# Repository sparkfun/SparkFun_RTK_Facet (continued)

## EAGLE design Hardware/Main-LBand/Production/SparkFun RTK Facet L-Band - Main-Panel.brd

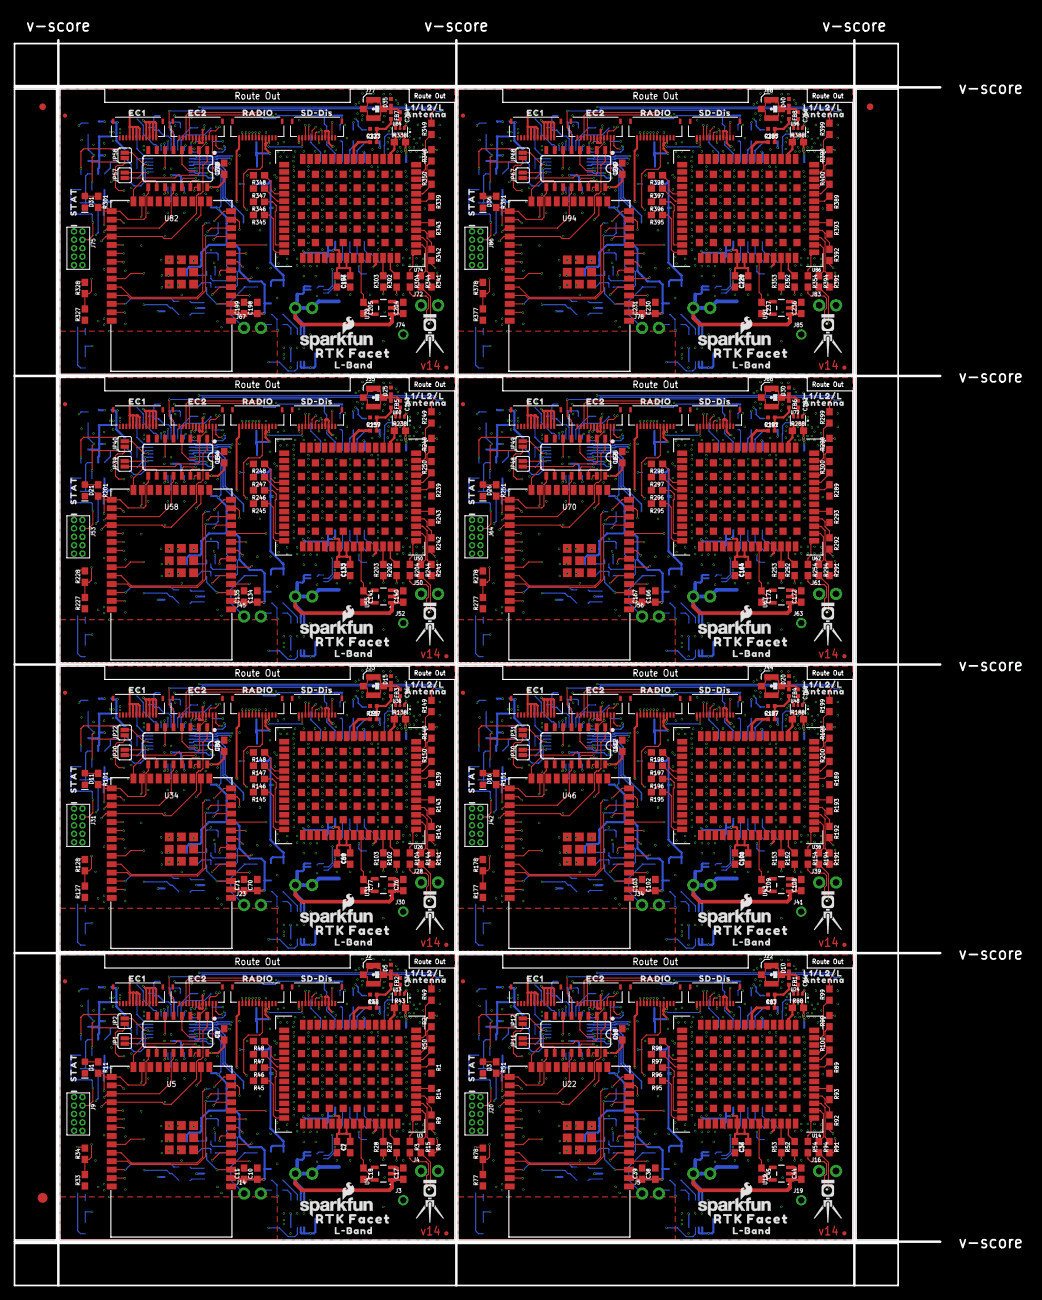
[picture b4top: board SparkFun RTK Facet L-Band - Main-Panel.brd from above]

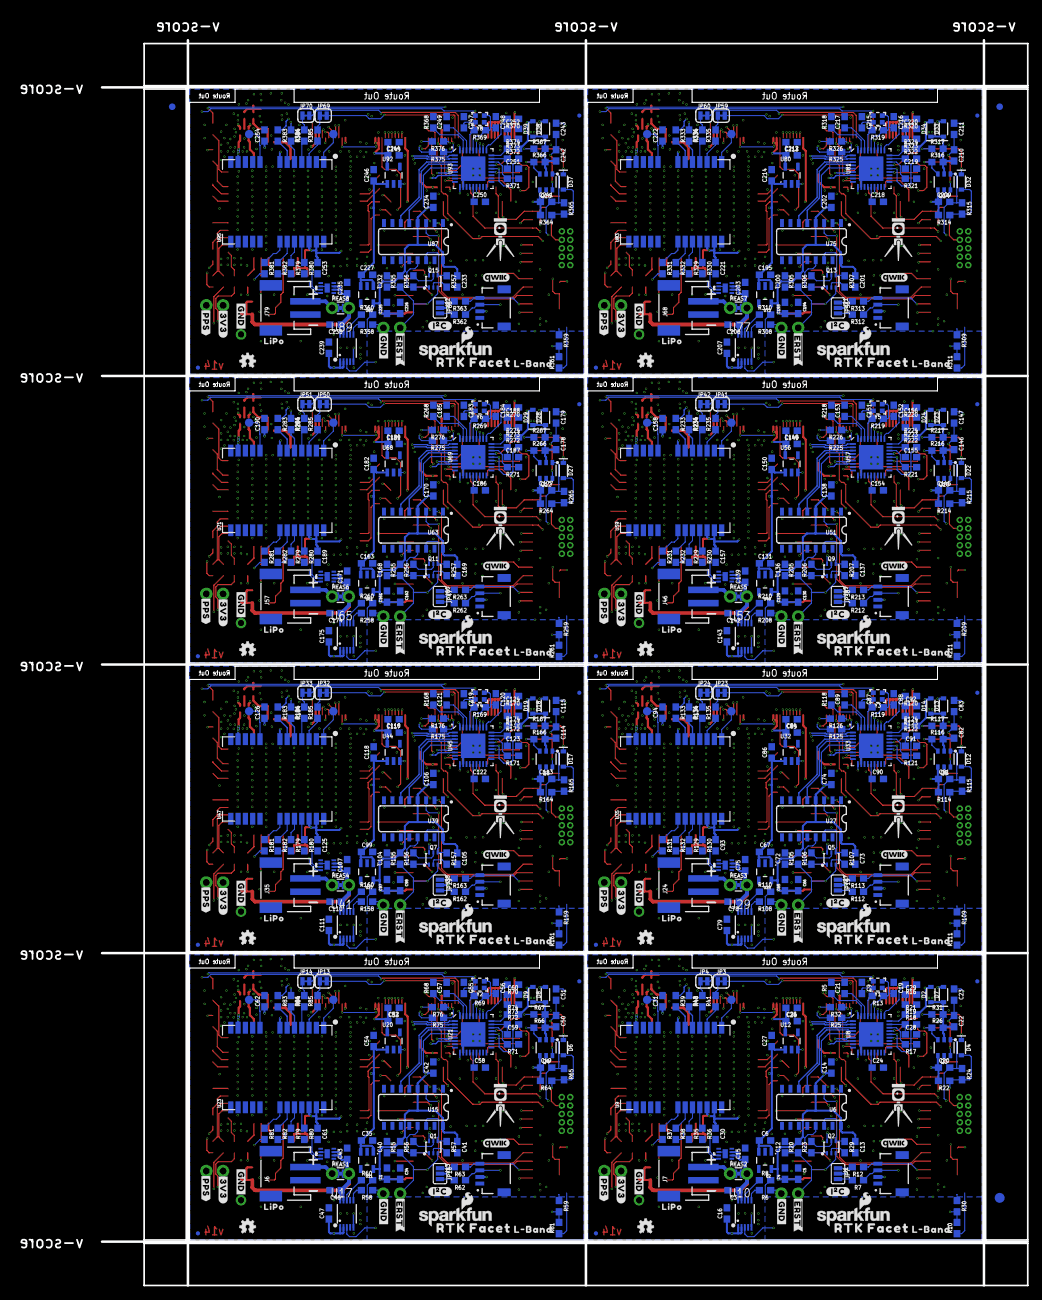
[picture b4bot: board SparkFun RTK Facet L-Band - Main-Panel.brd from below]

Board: 4 copper layers, 139.6 x 187.7 mm, 1206 parts (715 on the bottom side), 872 nets.

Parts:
C1, C2, C4, C6, C17, C18, C25, C27, C30, C31, C35, C36, C44, C45, C52, C54, C61, C62, C65, C67, C68, C76, C77, C84, C86, C93, C94, C97, C99, C100, C108, C109, C116, C118, C125, C126, C129, C131, C132, C140, C141, C148, C150, C157, C158, C161, C163, C164, C172, C173, C180, C182, C189, C190, C193, C195, C196, C204, C205, C212, C214, C221, C222, C225, C227, C228, C236, C237, C244, C246, C253, C254: 1.0uF; 0603
C3, C16, C46, C47, C78, C79, C110, C111, C142, C143, C174, C175, C206, C207, C238, C239: 4.7uF; 0603
C5, C7, C8, C11, C12, C13, C15, C21, C22, C23, C24, C26, C28, C29, C34, C37, C39, C40, C41, C43, C48, C50, C51, C53, C57, C58, C59, C60, C66, C69, C71, C72, C73, C75, C80, C82, C83, C85, C89, C90, C91, C92, C98, C101, C103, C104, C105, C107, C112, C114, C115, C117, C121, C122, C123, C124, C130, C133, C135, C136, C137, C139, C144, C146, C147, C149, C153, C154, C155, C156, C162, C165, C167, C168, C169, C171, C176, C178, C179, C181, C185, C186, C187, C188, C194, C197, C199, C200, C201, C203, C208, C210, C211, C213, C217, C218, C219, C220, C226, C229, C231, C232, C233, C235, C240, C242, C243, C245, C249, C250, C251, C252: 0.1uF; 0603
C9, C19, C55, C56, C87, C88, C119, C120, C151, C152, C183, C184, C215, C216, C247, C248: 18pF; 0603
C10, C14, C20, C38, C42, C49, C70, C74, C81, C102, C106, C113, C134, C138, C145, C166, C170, C177, C198, C202, C209, C230, C234, C241: 10uF; 0603
C32, C33, C63, C64, C95, C96, C127, C128, C159, C160, C191, C192, C223, C224, C255, C256: 47pF; 0402-TIGHT
D1, D3, D11, D16, D21, D26, D31, D36: Yellow; LED-0603
D2, D7, D8, D9, D13, D14, D18, D19, D23, D24, D28, D29, D33, D34, D38, D39: 3A/10V/280mV; SOD-323
D4, D6, D12, D17, D22, D27, D32, D37: 250mA/100V; SOD-323
D5, D10, D15, D20, D25, D30, D35, D40: PESD0402; 0402-TIGHT
E$1, E$2, E$3, E$4: FIDUCIAL-1X2
E$5, E$6: FIDUCIAL-1.5X3
FB1, FB2, FB3, FB4, FB5, FB6, FB7, FB8: 2.66Ω; 0402-TIGHT
J1, J13, J27, J38, J49, J60, J71, J82: QWIIC_RIGHT_ANGLE; JST04_1MM_RA
J2, J22, J33, J44, J55, J66, J77, J88: U.FL
J3, J19, J30, J41, J52, J63, J74, J85: 1X01_NO_SILK
J4, J5, J14, J16, J23, J28, J34, J39, J45, J50, J56, J61, J67, J72, J78, J83: 1X02_NO_SILK
J6, J7, J24, J35, J46, J57, J68, J79: JST-2-SMD
J8, J10, J11, J12, J15, J17, J18, J21, J25, J26, J29, J32, J36, J37, J40, J43, J47, J48, J51, J54, J58, J59, J62, J65, J69, J70, J73, J76, J80, J81, J84, J87: FPC_12_DOUBLESIDED_BACKFLIP
J9, J20, J31, J42, J53, J64, J75, J86: CORTEX_JTAG_DEBUG_PTH; 2X5-PTH-1.27MM
JP1, JP2, JP11, JP12, JP20, JP22, JP30, JP31, JP39, JP40, JP48, JP49, JP57, JP58, JP67, JP68: SMT-JUMPER_2_NO_SILK
JP3, JP4, JP13, JP14, JP23, JP24, JP32, JP33, JP41, JP42, JP50, JP51, JP59, JP60, JP69, JP70: SMT-JUMPER_2_NC_TRACE_SILK
JP5, JP6, JP8, JP9, JP15, JP16, JP17, JP18, JP21, JP25, JP26, JP27, JP28, JP34, JP35, JP36, JP37, JP43, JP44, JP45, JP46, JP52, JP53, JP54, JP55, JP61, JP62, JP63, JP64, JP65, JP71, JP81: FIDUCIALUFIDUCIAL; FIDUCIAL-MICRO
JP7, JP10, JP19, JP29, JP38, JP47, JP56, JP66: JUMPER-SMT_3_NO_SILK; SMT-JUMPER_3_NO_SILK
LOGO1, LOGO4, LOGO7, LOGO10, LOGO13, LOGO16, LOGO19, LOGO22: OSHW-LOGOMINI; OSHW-LOGO-MINI
LOGO2, LOGO3, LOGO5, LOGO6, LOGO8, LOGO9, LOGO11, LOGO12, LOGO14, LOGO15, LOGO17, LOGO18, LOGO20, LOGO21, LOGO23, LOGO24: SFE_LOGO_NAME_FLAME.1_INCH; SFE_LOGO_NAME_FLAME_.1
MEAS1, MEAS2, MEAS3, MEAS4, MEAS5, MEAS6, MEAS7, MEAS8: JUMPER-COMBO_2_NC_TRACE; COMBO-JUMPER_2_NC_TRACE
Q1, Q2, Q5, Q7, Q9, Q11, Q13, Q15: MBT3904DW1T1; SC70-6
Q3, Q4, Q6, Q8, Q10, Q12, Q14, Q16: SIL2308; SOT26
R1, R2, R3, R4, R9, R14, R15, R35, R36, R37, R38, R41, R42, R45, R46, R47, R48, R49, R50, R54, R79, R80, R81, R82, R85, R86, R89, R90, R91, R92, R93, R94, R95, R96, R97, R98, R99, R100, R104, R129, R130, R131, R132, R135, R136, R139, R140, R141, R142, R143, R144, R145, R146, R147, R148, R149, R150, R154, R179, R180, R181, R182, R185, R186, R189, R190, R191, R192, R193, R194, R195, R196, R197, R198, R199, R200, R204, R229, R230, R231, R232, R235, R236, R239, R240, R241, R242, R243, R244, R245, R246, R247, R248, R249, R250, R254, R279, R280, R281, R282, R285, R286, R289, R290, R291, R292, R293, R294, R295, R296, R297, R298, R299, R300, R304, R329, R330, R331, R332, R335, R336, R339, R340, R341, R342, R343, R344, R345, R346, R347, R348, R349, R350, R354, R379, R380, R381, R382, R385, R386, R389, R390, R391, R392, R393, R394, R395, R396, R397, R398, R399, R400: 33; 0603
R5, R68, R118, R168, R218, R268, R318, R368: 12k; 0603
R6, R11, R51, R58, R101, R108, R151, R158, R201, R208, R251, R258, R301, R308, R351, R358: 1k; 0603
R7, R12, R62, R63, R112, R113, R162, R163, R212, R213, R262, R263, R312, R313, R362, R363: 2.2k; 0603
R8, R60, R110, R160, R210, R260, R310, R360: 0; 0603
R10, R20, R22, R23, R29, R31, R34, R55, R56, R57, R61, R64, R67, R78, R105, R106, R107, R111, R114, R117, R128, R155, R156, R157, R161, R164, R167, R178, R205, R206, R207, R211, R214, R217, R228, R255, R256, R257, R261, R264, R267, R278, R305, R306, R307, R311, R314, R317, R328, R355, R356, R357, R361, R364, R367, R378: 10k; 0603
R13, R69, R119, R169, R219, R269, R319, R369: 1M; 0603
R16, R17, R18, R19, R21, R26, R33, R66, R70, R71, R72, R73, R74, R77, R116, R120, R121, R122, R123, R124, R127, R166, R170, R171, R172, R173, R174, R177, R216, R220, R221, R222, R223, R224, R227, R266, R270, R271, R272, R273, R274, R277, R316, R320, R321, R322, R323, R324, R327, R366, R370, R371, R372, R373, R374, R377: 100k; 0603
R24, R65, R115, R165, R215, R265, R315, R365: 300k; 0603
R25, R32, R75, R76, R125, R126, R175, R176, R225, R226, R275, R276, R325, R326, R375, R376: 22; 0603
R27, R28, R39, R40, R52, R53, R83, R84, R102, R103, R133, R134, R152, R153, R183, R184, R202, R203, R233, R234, R252, R253, R283, R284, R302, R303, R333, R334, R352, R353, R383, R384: 27; 0603
R30, R59, R109, R159, R209, R259, R309, R359: 150k; 0603
R43, R88, R138, R188, R238, R288, R338, R388: 100; 0603
R44, R87, R137, R187, R237, R287, R337, R387: 10; 0402-TIGHT
TP1, TP2, TP3, TP4, TP5, TP6, TP7, TP8, TP9, TP10, TP11, TP12, TP13, TP14, TP15, TP16: TEST-POINT3X5; PAD.03X.05
U1, U18, U30, U42, U54, U66, U78, U90: 74HC4052D; SO16
U2, U11, U12, U20, U25, U32, U37, U44, U49, U56, U61, U68, U73, U80, U85, U92: AP2112K-3.3V; SOT23-5
U3, U14, U26, U38, U50, U62, U74, U86: U-BLOX_ZED-F9P; ZED-F9P
U4, U19, U31, U43, U55, U67, U79, U91: STLQ015-3.3V; SOT23-5
U5, U22, U34, U46, U58, U70, U82, U94: ESP-WROOM-3232D-DFMP; ESP-WROOM-32D-DFM_PASTE
U6, U15, U27, U39, U51, U63, U75, U87: CH340C; SO016
U7, U16, U28, U40, U52, U64, U76, U88: MAX17048; DFN-8
U8, U21, U33, U45, U57, U69, U81, U93: USB251XB; QFN-36
U9, U23, U35, U47, U59, U71, U83, U95: U-BLOX_NEO-D9S-00B; NEO-M9N/M8T/M8U/D9S/F9P
U10, U17, U29, U41, U53, U65, U77, U89: MCP73833MSOP; MSOP10
U13, U24, U36, U48, U60, U72, U84, U96: POWER-DIVIDER; PD0922J5050S2HF_ANA
U$1, U$22, U$47, U$68, U$90, U$111, U$132, U$153: LIPO0
U$2, U$30, U$42, U$63, U$85, U$106, U$127, U$148: QWIIC_4MM
U$3, U$20, U$45, U$66, U$88, U$109, U$130, U$151: EC21
U$4, U$21, U$46, U$67, U$89, U$110, U$131, U$152: SD#DIS0
U$5, U$7, U$40, U$41, U$61, U$62, U$82, U$83, U$104, U$105, U$125, U$126, U$146, U$147, U$167, U$168: L#BAND0
U$6, U$23, U$48, U$69, U$91, U$112, U$133, U$154: #3V3#0
U$8, U$19, U$44, U$65, U$87, U$108, U$129, U$150: EC10
U$9, U$14, U$35, U$43, U$56, U$64, U$77, U$84, U$86, U$99, U$107, U$120, U$128, U$141, U$149, U$162: #GND#1
U$10, U$27, U$49, U$70, U$92, U$113, U$134, U$155: #PPS#1
U$11, U$13, U$32, U$34, U$53, U$55, U$74, U$76, U$96, U$98, U$117, U$119, U$138, U$140, U$159, U$161: RTK_FACET0
U$12, U$33, U$54, U$75, U$97, U$118, U$139, U$160: RADIO0
U$15, U$16, U$36, U$37, U$57, U$58, U$78, U$79, U$100, U$101, U$121, U$122, U$142, U$143, U$163, U$164: RTK5#SVG0
U$17, U$38, U$59, U$80, U$102, U$123, U$144, U$165: ANTENNA1
U$18, U$39, U$60, U$81, U$103, U$124, U$145, U$166: L1#L2#L0
U$24, U$28, U$50, U$71, U$93, U$114, U$135, U$156: STAT0
U$25, U$29, U$51, U$72, U$94, U$115, U$136, U$157: #I�C#0
U$26, U$31, U$52, U$73, U$95, U$116, U$137, U$158: ##ERST##0
Y1, Y2, Y3, Y4, Y5, Y6, Y7, Y8: 24MHz; CRYSTAL-SMD-2.0X1.6MM

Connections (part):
3.3V: C2.1, C7.2, C8.1, C25.1, C26.2, C30.1, C31.1, J1.2, J4.1, J8.3, J8.4, J10.3, J10.4, J18.5, J18.6, JP7.2, U1.16, U3.33, U3.34, U3.38, U9.7, U9.22, U9.23, U12.5
3.3V1: C36.1, C37.2, C48.1, C52.1, C53.2, C61.1, C62.1, J12.5, J12.6, J13.2, J16.1, J17.3, J17.4, J21.3, J21.4, JP10.2, U14.33, U14.34, U14.38, U18.16, U20.5, U23.7, U23.22, U23.23
3.3V2: C68.1, C69.2, C80.1, C84.1, C85.2, C93.1, C94.1, J26.5, J26.6, J27.2, J28.1, J29.3, J29.4, J32.3, J32.4, JP19.2, U26.33, U26.34, U26.38, U30.16, U32.5, U35.7, U35.22, U35.23
3.3V3: C100.1, C101.2, C112.1, C116.1, C117.2, C125.1, C126.1, J37.5, J37.6, J38.2, J39.1, J40.3, J40.4, J43.3, J43.4, JP29.2, U38.33, U38.34, U38.38, U42.16, U44.5, U47.7, U47.22, U47.23
3.3V4: C132.1, C133.2, C144.1, C148.1, C149.2, C157.1, C158.1, J48.5, J48.6, J49.2, J50.1, J51.3, J51.4, J54.3, J54.4, JP38.2, U50.33, U50.34, U50.38, U54.16, U56.5, U59.7, U59.22, U59.23
3.3V5: C164.1, C165.2, C176.1, C180.1, C181.2, C189.1, C190.1, J59.5, J59.6, J60.2, J61.1, J62.3, J62.4, J65.3, J65.4, JP47.2, U62.33, U62.34, U62.38, U66.16, U68.5, U71.7, U71.22, U71.23
3.3V6: C196.1, C197.2, C208.1, C212.1, C213.2, C221.1, C222.1, J70.5, J70.6, J71.2, J72.1, J73.3, J73.4, J76.3, J76.4, JP56.2, U74.33, U74.34, U74.38, U78.16, U80.5, U83.7, U83.22, U83.23
3.3V7: C228.1, C229.2, C240.1, C244.1, C245.2, C253.1, C254.1, J81.5, J81.6, J82.2, J83.1, J84.3, J84.4, J87.3, J87.4, JP66.2, U86.33, U86.34, U86.38, U90.16, U92.5, U95.7, U95.22, U95.23
CHG_LED: J8.11, U10.3
CHG_LED1: J17.11, U17.3
CHG_LED2: J29.11, U29.3
CHG_LED3: J40.11, U41.3
CHG_LED4: J51.11, U53.3
CHG_LED5: J62.11, U65.3
CHG_LED6: J73.11, U77.3
CHG_LED7: J84.11, U89.3
CHG_THERM1: R8.2, R10.2, R30.2
CHG_THERM2: R59.2, R60.2, R61.2
CHG_THERM3: R109.2, R110.2, R111.2
CHG_THERM4: R159.2, R160.2, R161.2
CHG_THERM5: R209.2, R210.2, R211.2
CHG_THERM6: R259.2, R260.2, R261.2
CHG_THERM7: R309.2, R310.2, R311.2
CHG_THERM8: R359.2, R360.2, R361.2
ESP32_!DTR: Q2.1, R23.1, U6.13
ESP32_!DTR1: Q1.1, R56.1, U15.13
ESP32_!DTR2: Q5.1, R106.1, U27.13
ESP32_!DTR3: Q7.1, R156.1, U39.13
ESP32_!DTR4: Q9.1, R206.1, U51.13
ESP32_!DTR5: Q11.1, R256.1, U63.13
ESP32_!DTR6: Q13.1, R306.1, U75.13
ESP32_!DTR7: Q15.1, R356.1, U87.13
ESP32_!RTS: Q2.4, R29.1, U6.14
ESP32_!RTS1: Q1.4, R57.1, U15.14
ESP32_!RTS2: Q5.4, R107.1, U27.14
ESP32_!RTS3: Q7.4, R157.1, U39.14
ESP32_!RTS4: Q9.4, R207.1, U51.14
ESP32_!RTS5: Q11.4, R257.1, U63.14
ESP32_!RTS6: Q13.4, R307.1, U75.14
ESP32_!RTS7: Q15.4, R357.1, U87.14
ESP32_EN: C12.1, J9.10, J14.1, Q2.3, R20.1, U5.3
ESP32_EN1: C40.1, J5.1, J20.10, Q1.3, R55.1, U22.3
ESP32_EN2: C72.1, J23.1, J31.10, Q5.3, R105.1, U34.3
ESP32_EN3: C104.1, J34.1, J42.10, Q7.3, R155.1, U46.3
ESP32_EN4: C136.1, J45.1, J53.10, Q9.3, R205.1, U58.3
ESP32_EN5: C168.1, J56.1, J64.10, Q11.3, R255.1, U70.3
ESP32_EN6: C200.1, J67.1, J75.10, Q13.3, R305.1, U82.3
ESP32_EN7: C232.1, J78.1, J86.10, Q15.3, R355.1, U94.3
ESP32_RXI: U5.34, U6.2
ESP32_RXI1: U15.2, U22.34
ESP32_RXI2: U27.2, U34.34
ESP32_RXI3: U39.2, U46.34
ESP32_RXI4: U51.2, U58.34
ESP32_RXI5: U63.2, U70.34
ESP32_RXI6: U75.2, U82.34
ESP32_RXI7: U87.2, U94.34
ESP32_TXO: U5.35, U6.3
ESP32_TXO1: U15.3, U22.35
ESP32_TXO2: U27.3, U34.35
ESP32_TXO3: U39.3, U46.35
ESP32_TXO4: U51.3, U58.35
ESP32_TXO5: U63.3, U70.35
ESP32_TXO6: U75.3, U82.35
ESP32_TXO7: U87.3, U94.35
ESP_0/BOOT/STAT_LED/MUX_B: Q2.6, R11.2, U1.9, U5.25
ESP_0/BOOT/STAT_LED/MUX_B1: Q1.6, R51.2, U18.9, U22.25
ESP_0/BOOT/STAT_LED/MUX_B2: Q5.6, R101.2, U30.9, U34.25
ESP_0/BOOT/STAT_LED/MUX_B3: Q7.6, R151.2, U42.9, U46.25
ESP_0/BOOT/STAT_LED/MUX_B4: Q9.6, R201.2, U54.9, U58.25
ESP_0/BOOT/STAT_LED/MUX_B5: Q11.6, R251.2, U66.9, U70.25
ESP_0/BOOT/STAT_LED/MUX_B6: Q13.6, R301.2, U78.9, U82.25
ESP_0/BOOT/STAT_LED/MUX_B7: Q15.6, R351.2, U90.9, U94.25
ESP_2/MUX_A: U1.10, U5.24
ESP_2/MUX_A1: U18.10, U22.24
ESP_2/MUX_A2: U30.10, U34.24
ESP_2/MUX_A3: U42.10, U46.24
ESP_2/MUX_A4: U54.10, U58.24
ESP_2/MUX_A5: U66.10, U70.24
ESP_2/MUX_A6: U78.10, U82.24
ESP_2/MUX_A7: U90.10, U94.24
ESP_3V1: C1.1, C34.2, C38.1, C39.1, C41.1, C42.1, J20.1, R55.2, R72.2, R78.2, U11.5, U15.4, U15.16, U21.5, U21.10, U21.15, U21.23, U21.29, U21.36, U22.2
ESP_3V2: C65.1, C66.2, C70.1, C71.1, C73.1, C74.1, J31.1, R105.2, R122.2, R128.2, U25.5, U27.4, U27.16, U33.5, U33.10, U33.15, U33.23, U33.29, U33.36, U34.2
ESP_3V3: C4.1, C5.2, C10.1, C11.1, C13.1, C14.1, J9.1, R18.2, R20.2, R34.2, U2.5, U5.2, U6.4, U6.16, U8.5, U8.10, U8.15, U8.23, U8.29, U8.36
ESP_3V4: C97.1, C98.2, C102.1, C103.1, C105.1, C106.1, J42.1, R155.2, R172.2, R178.2, U37.5, U39.4, U39.16, U45.5, U45.10, U45.15, U45.23, U45.29, U45.36, U46.2
ESP_3V5: C129.1, C130.2, C134.1, C135.1, C137.1, C138.1, J53.1, R205.2, R222.2, R228.2, U49.5, U51.4, U51.16, U57.5, U57.10, U57.15, U57.23, U57.29, U57.36, U58.2
ESP_3V6: C161.1, C162.2, C166.1, C167.1, C169.1, C170.1, J64.1, R255.2, R272.2, R278.2, U61.5, U63.4, U63.16, U69.5, U69.10, U69.15, U69.23, U69.29, U69.36, U70.2
ESP_3V7: C193.1, C194.2, C198.1, C199.1, C201.1, C202.1, J75.1, R305.2, R322.2, R328.2, U73.5, U75.4, U75.16, U81.5, U81.10, U81.15, U81.23, U81.29, U81.36, U82.2
ESP_3V8: C225.1, C226.2, C230.1, C231.1, C233.1, C234.1, J86.1, R355.2, R372.2, R378.2, U85.5, U87.4, U87.16, U93.5, U93.10, U93.15, U93.23, U93.29, U93.36, U94.2
ESP_4/RADIO_PWR_ON: J10.6, U5.26
ESP_4/RADIO_PWR_ON1: J21.6, U22.26
ESP_4/RADIO_PWR_ON2: J32.6, U34.26
ESP_4/RADIO_PWR_ON3: J43.6, U46.26
ESP_4/RADIO_PWR_ON4: J54.6, U58.26
ESP_4/RADIO_PWR_ON5: J65.6, U70.26
ESP_4/RADIO_PWR_ON6: J76.6, U82.26
ESP_4/RADIO_PWR_ON7: J87.6, U94.26
ESP_5/RADIO_CTSI: J10.8, U5.29
ESP_5/RADIO_CTSI1: J21.8, U22.29
ESP_5/RADIO_CTSI2: J32.8, U34.29
ESP_5/RADIO_CTSI3: J43.8, U46.29
ESP_5/RADIO_CTSI4: J54.8, U58.29
ESP_5/RADIO_CTSI5: J65.8, U70.29
ESP_5/RADIO_CTSI6: J76.8, U82.29
ESP_5/RADIO_CTSI7: J87.8, U94.29
ESP_12/MTDI: J9.8, U5.14
ESP_12/MTDI1: J20.8, U22.14
ESP_12/MTDI2: J31.8, U34.14
ESP_12/MTDI3: J42.8, U46.14
ESP_12/MTDI4: J53.8, U58.14
ESP_12/MTDI5: J64.8, U70.14
ESP_12/MTDI6: J75.8, U82.14
ESP_12/MTDI7: J86.8, U94.14
ESP_13/POWER_CTRL/MTCK: D4.A, J9.4, R22.1, R24.2, U5.16
ESP_13/POWER_CTRL/MTCK1: D6.A, J20.4, R64.1, R65.2, U22.16
ESP_13/POWER_CTRL/MTCK2: D12.A, J31.4, R114.1, R115.2, U34.16
ESP_13/POWER_CTRL/MTCK3: D17.A, J42.4, R164.1, R165.2, U46.16
ESP_13/POWER_CTRL/MTCK4: D22.A, J53.4, R214.1, R215.2, U58.16
ESP_13/POWER_CTRL/MTCK5: D27.A, J64.4, R264.1, R265.2, U70.16
ESP_13/POWER_CTRL/MTCK6: D32.A, J75.4, R314.1, R315.2, U82.16
ESP_13/POWER_CTRL/MTCK7: D37.A, J86.4, R364.1, R365.2, U94.16
ESP_14/PERIPHERAL_POWER/MTMS: J9.2, U5.13, U12.3
ESP_14/PERIPHERAL_POWER/MTMS1: J20.2, U20.3, U22.13
ESP_14/PERIPHERAL_POWER/MTMS2: J31.2, U32.3, U34.13
ESP_14/PERIPHERAL_POWER/MTMS3: J42.2, U44.3, U46.13
ESP_14/PERIPHERAL_POWER/MTMS4: J53.2, U56.3, U58.13
ESP_14/PERIPHERAL_POWER/MTMS5: J64.2, U68.3, U70.13
ESP_14/PERIPHERAL_POWER/MTMS6: J75.2, U80.3, U82.13
ESP_14/PERIPHERAL_POWER/MTMS7: J86.2, U92.3, U94.13
ESP_15/MTDO/RADIO_!RESET!: J9.6, J10.5, U5.23
ESP_15/MTDO/RADIO_!RESET!1: J20.6, J21.5, U22.23
ESP_15/MTDO/RADIO_!RESET!2: J31.6, J32.5, U34.23
ESP_15/MTDO/RADIO_!RESET!3: J42.6, J43.5, U46.23
ESP_15/MTDO/RADIO_!RESET!4: J53.6, J54.5, U58.23
ESP_15/MTDO/RADIO_!RESET!5: J64.6, J65.5, U70.23
ESP_15/MTDO/RADIO_!RESET!6: J75.6, J76.5, U82.23
ESP_15/MTDO/RADIO_!RESET!7: J86.6, J87.5, U94.23
ESP_16/ZED_TXO1: R3.2, U1.12, U5.27
ESP_16/ZED_TXO2: R54.2, U18.12, U22.27
ESP_16/ZED_TXO3: R104.2, U30.12, U34.27
ESP_16/ZED_TXO4: R154.2, U42.12, U46.27
ESP_16/ZED_TXO5: R204.2, U54.12, U58.27
ESP_16/ZED_TXO6: R254.2, U66.12, U70.27
ESP_16/ZED_TXO7: R304.2, U78.12, U82.27
ESP_16/ZED_TXO8: R354.2, U90.12, U94.27
ESP_17/ZED_RXI1: R15.2, U1.1, U5.28
ESP_17/ZED_RXI2: R94.2, U18.1, U22.28
ESP_17/ZED_RXI3: R144.2, U30.1, U34.28
ESP_17/ZED_RXI4: R194.2, U42.1, U46.28
ESP_17/ZED_RXI5: R244.2, U54.1, U58.28
ESP_17/ZED_RXI6: R294.2, U66.1, U70.28
ESP_17/ZED_RXI7: R344.2, U78.1, U82.28
ESP_17/ZED_RXI8: R394.2, U90.1, U94.28
ESP_18/SD_SCK: J8.7, U5.30
ESP_18/SD_SCK1: J17.7, U22.30
ESP_18/SD_SCK2: J29.7, U34.30
ESP_18/SD_SCK3: J40.7, U46.30
ESP_18/SD_SCK4: J51.7, U58.30
ESP_18/SD_SCK5: J62.7, U70.30
ESP_18/SD_SCK6: J73.7, U82.30
ESP_18/SD_SCK7: J84.7, U94.30
ESP_19/SD_CIPO: J8.8, U5.31
ESP_19/SD_CIPO1: J17.8, U22.31
ESP_19/SD_CIPO2: J29.8, U34.31
ESP_19/SD_CIPO3: J40.8, U46.31
ESP_19/SD_CIPO4: J51.8, U58.31
ESP_19/SD_CIPO5: J62.8, U70.31
ESP_19/SD_CIPO6: J73.8, U82.31
ESP_19/SD_CIPO7: J84.8, U94.31
ESP_21/SDA: J1.3, J8.10, J18.4, JP1.1, R4.2, R7.1, R37.2, U1.2, U5.33, U7.8
ESP_21/SDA1: J12.4, J13.3, J17.10, JP11.1, R62.1, R81.2, R91.2, U16.8, U18.2, U22.33
ESP_21/SDA2: J26.4, J27.3, J29.10, JP20.1, R112.1, R131.2, R141.2, U28.8, U30.2, U34.33
ESP_21/SDA3: J37.4, J38.3, J40.10, JP30.1, R162.1, R181.2, R191.2, U40.8, U42.2, U46.33
ESP_21/SDA4: J48.4, J49.3, J51.10, JP39.1, R212.1, R231.2, R241.2, U52.8, U54.2, U58.33
ESP_21/SDA5: J59.4, J60.3, J62.10, JP48.1, R262.1, R281.2, R291.2, U64.8, U66.2, U70.33
ESP_21/SDA6: J70.4, J71.3, J73.10, JP57.1, R312.1, R331.2, R341.2, U76.8, U78.2, U82.33
ESP_21/SDA7: J81.4, J82.3, J84.10, JP67.1, R362.1, R381.2, R391.2, U88.8, U90.2, U94.33
ESP_22/SCL: J1.4, J8.9, J18.3, JP2.1, R9.2, R12.1, R38.2, U1.15, U5.36, U7.7
ESP_22/SCL1: J12.3, J13.4, J17.9, JP12.1, R63.1, R82.2, R92.2, U16.7, U18.15, U22.36
ESP_22/SCL2: J26.3, J27.4, J29.9, JP22.1, R113.1, R132.2, R142.2, U28.7, U30.15, U34.36
ESP_22/SCL3: J37.3, J38.4, J40.9, JP31.1, R163.1, R182.2, R192.2, U40.7, U42.15, U46.36
ESP_22/SCL4: J48.3, J49.4, J51.9, JP40.1, R213.1, R232.2, R242.2, U52.7, U54.15, U58.36
ESP_22/SCL5: J59.3, J60.4, J62.9, JP49.1, R263.1, R282.2, R292.2, U64.7, U66.15, U70.36
ESP_22/SCL6: J70.3, J71.4, J73.9, JP58.1, R313.1, R332.2, R342.2, U76.7, U78.15, U82.36
ESP_22/SCL7: J81.3, J82.4, J84.9, JP68.1, R363.1, R382.2, R392.2, U88.7, U90.15, U94.36
ESP_23/SD_COPI: J8.6, U5.37
ESP_23/SD_COPI1: J17.6, U22.37
ESP_23/SD_COPI2: J29.6, U34.37
ESP_23/SD_COPI3: J40.6, U46.37
ESP_23/SD_COPI4: J51.6, U58.37
ESP_23/SD_COPI5: J62.6, U70.37
ESP_23/SD_COPI6: J73.6, U82.37
ESP_23/SD_COPI7: J84.6, U94.37
ESP_25/SD_!CS!: J8.5, U5.10
ESP_25/SD_!CS!1: J17.5, U22.10
ESP_25/SD_!CS!2: J29.5, U34.10
ESP_25/SD_!CS!3: J40.5, U46.10
ESP_25/SD_!CS!4: J51.5, U58.10
ESP_25/SD_!CS!5: J62.5, U70.10
ESP_25/SD_!CS!6: J73.5, U82.10
ESP_25/SD_!CS!7: J84.5, U94.10
ESP_26/DAC1: U18.11, U22.11
ESP_26/DAC2: U1.11, U5.11
ESP_26/DAC3: U30.11, U34.11
ESP_26/DAC4: U42.11, U46.11
ESP_26/DAC5: U54.11, U58.11
ESP_26/DAC6: U66.11, U70.11
ESP_26/DAC7: U78.11, U82.11
ESP_26/DAC8: U90.11, U94.11
ESP_27/FAST_OFF: C20.2, Q3.G1, R24.1, U5.12
ESP_27/FAST_OFF1: C49.2, Q4.G1, R65.1, U22.12
ESP_27/FAST_OFF2: C81.2, Q6.G1, R115.1, U34.12
ESP_27/FAST_OFF3: C113.2, Q8.G1, R165.1, U46.12
ESP_27/FAST_OFF4: C145.2, Q10.G1, R215.1, U58.12
ESP_27/FAST_OFF5: C177.2, Q12.G1, R265.1, U70.12
ESP_27/FAST_OFF6: C209.2, Q14.G1, R315.1, U82.12
ESP_27/FAST_OFF7: C241.2, Q16.G1, R365.1, U94.12
ESP_32/RADIO_TXO: J10.11, U5.8
ESP_32/RADIO_TXO1: J21.11, U22.8
ESP_32/RADIO_TXO2: J32.11, U34.8
ESP_32/RADIO_TXO3: J43.11, U46.8
ESP_32/RADIO_TXO4: J54.11, U58.8
ESP_32/RADIO_TXO5: J65.11, U70.8
ESP_32/RADIO_TXO6: J76.11, U82.8
ESP_32/RADIO_TXO7: J87.11, U94.8
ESP_33/RADIO_RXI: J10.10, U5.9
ESP_33/RADIO_RXI1: J21.10, U22.9
ESP_33/RADIO_RXI2: J32.10, U34.9
ESP_33/RADIO_RXI3: J43.10, U46.9
ESP_33/RADIO_RXI4: J54.10, U58.9
ESP_33/RADIO_RXI5: J65.10, U70.9
ESP_33/RADIO_RXI6: J76.10, U82.9
ESP_33/RADIO_RXI7: J87.10, U94.9
ESP_DM: U6.6, U8.3
ESP_DM1: U15.6, U21.3
ESP_DM2: U27.6, U33.3
ESP_DM3: U39.6, U45.3
ESP_DM4: U51.6, U57.3
ESP_DM5: U63.6, U69.3
ESP_DM6: U75.6, U81.3
ESP_DM7: U87.6, U93.3
ESP_DP: U6.5, U8.4
ESP_DP1: U15.5, U21.4
ESP_DP2: U27.5, U33.4
ESP_DP3: U39.5, U45.4
ESP_DP4: U51.5, U57.4
ESP_DP5: U63.5, U69.4
ESP_DP6: U75.5, U81.4
ESP_DP7: U87.5, U93.4
ESP_I34/RADIO_INT: J10.7, U5.6
ESP_I34/RADIO_INT1: J21.7, U22.6
ESP_I34/RADIO_INT2: J32.7, U34.6
ESP_I34/RADIO_INT3: J43.7, U46.6
ESP_I34/RADIO_INT4: J54.7, U58.6
ESP_I34/RADIO_INT5: J65.7, U70.6
ESP_I34/RADIO_INT6: J76.7, U82.6
ESP_I34/RADIO_INT7: J87.7, U94.6
ESP_I35/DEVICE_SENSE: R33.2, R34.1, U5.7
ESP_I35/DEVICE_SENSE1: R77.2, R78.1, U22.7
ESP_I35/DEVICE_SENSE2: R127.2, R128.1, U34.7
ESP_I35/DEVICE_SENSE3: R177.2, R178.1, U46.7
ESP_I35/DEVICE_SENSE4: R227.2, R228.1, U58.7
ESP_I35/DEVICE_SENSE5: R277.2, R278.1, U70.7
ESP_I35/DEVICE_SENSE6: R327.2, R328.1, U82.7
ESP_I35/DEVICE_SENSE7: R377.2, R378.1, U94.7
ESP_I36/RADIO_RTSO: J10.9, U5.4
ESP_I36/RADIO_RTSO1: J21.9, U22.4
ESP_I36/RADIO_RTSO2: J32.9, U34.4
ESP_I36/RADIO_RTSO3: J43.9, U46.4
ESP_I36/RADIO_RTSO4: J54.9, U58.4
ESP_I36/RADIO_RTSO5: J65.9, U70.4
ESP_I36/RADIO_RTSO6: J76.9, U82.4
ESP_I36/RADIO_RTSO7: J87.9, U94.4
ESP_I39/ADC1: U18.4, U22.5
ESP_I39/ADC2: U30.4, U34.5
ESP_I39/ADC3: U42.4, U46.5
ESP_I39/ADC4: U54.4, U58.5
ESP_I39/ADC5: U66.4, U70.5
ESP_I39/ADC6: U78.4, U82.5
ESP_I39/ADC7: U90.4, U94.5
ESP_I39/ADC39: U1.4, U5.5
EXTERNAL_SERIAL1_RXI: J18.1, U1.3
EXTERNAL_SERIAL1_RXI1: J12.1, U18.3
EXTERNAL_SERIAL1_RXI2: J26.1, U30.3
EXTERNAL_SERIAL1_RXI3: J37.1, U42.3
EXTERNAL_SERIAL1_RXI4: J48.1, U54.3
EXTERNAL_SERIAL1_RXI5: J59.1, U66.3
EXTERNAL_SERIAL1_RXI6: J70.1, U78.3
EXTERNAL_SERIAL1_RXI7: J81.1, U90.3
EXTERNAL_SERIAL1_TXO: J18.2, U1.13
EXTERNAL_SERIAL1_TXO1: J12.2, U18.13
EXTERNAL_SERIAL1_TXO2: J26.2, U30.13
EXTERNAL_SERIAL1_TXO3: J37.2, U42.13
EXTERNAL_SERIAL1_TXO4: J48.2, U54.13
EXTERNAL_SERIAL1_TXO5: J59.2, U66.13
EXTERNAL_SERIAL1_TXO6: J70.2, U78.13
EXTERNAL_SERIAL1_TXO7: J81.2, U90.13
FENCE_LV: R48.1, U3.19
FENCE_LV1: R98.1, U14.19
FENCE_LV2: R148.1, U26.19
FENCE_LV3: R198.1, U38.19
FENCE_LV4: R248.1, U50.19
FENCE_LV5: R298.1, U62.19
FENCE_LV6: R348.1, U74.19
FENCE_LV7: R398.1, U86.19
GND: C2.2, C3.2, C4.2, C5.1, C6.2, C7.1, C8.2, C9.1, C10.2, C11.2, C12.2, C13.2, C14.2, C15.2, C16.2, C17.2, C18.2, C19.1, C21.2, C24.2, C25.2, C26.1, C27.2, C28.2, C29.2, C30.2, C31.2, C32.2, D1.C, D5.2, J1.1, J2.1, J2.2, J3.1, J7.1, J8.1, J9.3, J9.5, J9.7, J9.9, J10.1, J10.2, J14.2, J15.10, J15.11, J15.12, J18.11, J18.12, Q3.S1, R5.2, R6.1, R10.1, R16.1, R17.1, R19.1, R30.1, R33.1, U1.6, U1.7, U1.8, U2.2, U3.1, U3.3, U3.12, U3.14, U3.32, U3.37, U3.41, U3.48, U3.55, U3.56, U3.57, U3.58, U3.59, U3.60, U3.61, U3.62, U3.63, U3.64, U3.65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
GND1: C1.2, C34.1, C35.2, C36.2, C37.1, C38.2, C39.2, C40.2, C41.2, C42.2, C43.2, C44.2, C45.2, C46.2, C47.2, C48.2, C52.2, C53.1, C54.2, C55.1, C56.1, C57.2, C58.2, C59.2, C60.2, C61.2, C62.2, C63.2, D3.C, D10.2, J5.2, J6.1, J11.10, J11.11, J11.12, J12.11, J12.12, J13.1, J17.1, J19.1, J20.3, J20.5, J20.7, J20.9, J21.1, J21.2, J22.1, J22.2, Q4.S1, R58.1, R59.1, R61.1, R68.2, R70.1, R71.1, R73.1, R77.1, U11.2, U14.1, U14.3, U14.12, U14.14, U14.32, U14.37, U14.41, U14.48, U14.55, U14.56, U14.57, U14.58, U14.59, U14.60, U14.61, U14.62, U14.63, U14.64, U14.65, U14.66, U14.67, U14.68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
GND2: C65.2, C66.1, C67.2, C68.2, C69.1, C70.2, C71.2, C72.2, C73.2, C74.2, C75.2, C76.2, C77.2, C78.2, C79.2, C80.2, C84.2, C85.1, C86.2, C87.1, C88.1, C89.2, C90.2, C91.2, C92.2, C93.2, C94.2, C95.2, D11.C, D15.2, J23.2, J24.1, J25.10, J25.11, J25.12, J26.11, J26.12, J27.1, J29.1, J30.1, J31.3, J31.5, J31.7, J31.9, J32.1, J32.2, J33.1, J33.2, Q6.S1, R108.1, R109.1, R111.1, R118.2, R120.1, R121.1, R123.1, R127.1, U25.2, U26.1, U26.3, U26.12, U26.14, U26.32, U26.37, U26.41, U26.48, U26.55, U26.56, U26.57, U26.58, U26.59, U26.60, U26.61, U26.62, U26.63, U26.64, U26.65, U26.66, U26.67, U26.68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
GND3: C97.2, C98.1, C99.2, C100.2, C101.1, C102.2, C103.2, C104.2, C105.2, C106.2, C107.2, C108.2, C109.2, C110.2, C111.2, C112.2, C116.2, C117.1, C118.2, C119.1, C120.1, C121.2, C122.2, C123.2, C124.2, C125.2, C126.2, C127.2, D16.C, D20.2, J34.2, J35.1, J36.10, J36.11, J36.12, J37.11, J37.12, J38.1, J40.1, J41.1, J42.3, J42.5, J42.7, J42.9, J43.1, J43.2, J44.1, J44.2, Q8.S1, R158.1, R159.1, R161.1, R168.2, R170.1, R171.1, R173.1, R177.1, U37.2, U38.1, U38.3, U38.12, U38.14, U38.32, U38.37, U38.41, U38.48, U38.55, U38.56, U38.57, U38.58, U38.59, U38.60, U38.61, U38.62, U38.63, U38.64, U38.65, U38.66, U38.67, U38.68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
GND4: C129.2, C130.1, C131.2, C132.2, C133.1, C134.2, C135.2, C136.2, C137.2, C138.2, C139.2, C140.2, C141.2, C142.2, C143.2, C144.2, C148.2, C149.1, C150.2, C151.1, C152.1, C153.2, C154.2, C155.2, C156.2, C157.2, C158.2, C159.2, D21.C, D25.2, J45.2, J46.1, J47.10, J47.11, J47.12, J48.11, J48.12, J49.1, J51.1, J52.1, J53.3, J53.5, J53.7, J53.9, J54.1, J54.2, J55.1, J55.2, Q10.S1, R208.1, R209.1, R211.1, R218.2, R220.1, R221.1, R223.1, R227.1, U49.2, U50.1, U50.3, U50.12, U50.14, U50.32, U50.37, U50.41, U50.48, U50.55, U50.56, U50.57, U50.58, U50.59, U50.60, U50.61, U50.62, U50.63, U50.64, U50.65, U50.66, U50.67, U50.68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
GND5: C161.2, C162.1, C163.2, C164.2, C165.1, C166.2, C167.2, C168.2, C169.2, C170.2, C171.2, C172.2, C173.2, C174.2, C175.2, C176.2, C180.2, C181.1, C182.2, C183.1, C184.1, C185.2, C186.2, C187.2, C188.2, C189.2, C190.2, C191.2, D26.C, D30.2, J56.2, J57.1, J58.10, J58.11, J58.12, J59.11, J59.12, J60.1, J62.1, J63.1, J64.3, J64.5, J64.7, J64.9, J65.1, J65.2, J66.1, J66.2, Q12.S1, R258.1, R259.1, R261.1, R268.2, R270.1, R271.1, R273.1, R277.1, U61.2, U62.1, U62.3, U62.12, U62.14, U62.32, U62.37, U62.41, U62.48, U62.55, U62.56, U62.57, U62.58, U62.59, U62.60, U62.61, U62.62, U62.63, U62.64, U62.65, U62.66, U62.67, U62.68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
GND6: C193.2, C194.1, C195.2, C196.2, C197.1, C198.2, C199.2, C200.2, C201.2, C202.2, C203.2, C204.2, C205.2, C206.2, C207.2, C208.2, C212.2, C213.1, C214.2, C215.1, C216.1, C217.2, C218.2, C219.2, C220.2, C221.2, C222.2, C223.2, D31.C, D35.2, J67.2, J68.1, J69.10, J69.11, J69.12, J70.11, J70.12, J71.1, J73.1, J74.1, J75.3, J75.5, J75.7, J75.9, J76.1, J76.2, J77.1, J77.2, Q14.S1, R308.1, R309.1, R311.1, R318.2, R320.1, R321.1, R323.1, R327.1, U73.2, U74.1, U74.3, U74.12, U74.14, U74.32, U74.37, U74.41, U74.48, U74.55, U74.56, U74.57, U74.58, U74.59, U74.60, U74.61, U74.62, U74.63, U74.64, U74.65, U74.66, U74.67, U74.68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
GND7: C225.2, C226.1, C227.2, C228.2, C229.1, C230.2, C231.2, C232.2, C233.2, C234.2, C235.2, C236.2, C237.2, C238.2, C239.2, C240.2, C244.2, C245.1, C246.2, C247.1, C248.1, C249.2, C250.2, C251.2, C252.2, C253.2, C254.2, C255.2, D36.C, D40.2, J78.2, J79.1, J80.10, J80.11, J80.12, J81.11, J81.12, J82.1, J84.1, J85.1, J86.3, J86.5, J86.7, J86.9, J87.1, J87.2, J88.1, J88.2, Q16.S1, R358.1, R359.1, R361.1, R368.2, R370.1, R371.1, R373.1, R377.1, U85.2, U86.1, U86.3, U86.12, U86.14, U86.32, U86.37, U86.41, U86.48, U86.55, U86.56, U86.57, U86.58, U86.59, U86.60, U86.61, U86.62, U86.63, U86.64, U86.65, U86.66, U86.67, U86.68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
LIPO_RAW: J7.2, MEAS2.1, MEAS2.3
LIPO_RAW1: J6.2, MEAS1.1, MEAS1.3
LIPO_RAW2: J24.2, MEAS3.1, MEAS3.3
LIPO_RAW3: J35.2, MEAS4.1, MEAS4.3
LIPO_RAW4: J46.2, MEAS5.1, MEAS5.3
LIPO_RAW5: J57.2, MEAS6.1, MEAS6.3
LIPO_RAW6: J68.2, MEAS7.1, MEAS7.3
LIPO_RAW7: J79.2, MEAS8.1, MEAS8.3
unnamed: R8.1, U10.8
unnamed: D1.A, R11.1
unnamed: JP7.3, R7.2
unnamed: JP7.1, R12.2
unnamed: R2.1, U3.51
unnamed: C22.1, C23.2, Q3.D1, Q3.G2, R26.1
unnamed: C9.2, R13.2, U8.33, Y1.3
unnamed: C19.2, R13.1, U8.32, Y1.1
unnamed: R5.1, U8.35
unnamed: R16.2, U8.28
unnamed: R27.2, U3.40
unnamed: R28.2, U3.39
unnamed: JP3.1, R41.2
unnamed: R17.2, U8.25
unnamed: C21.1, U8.34
unnamed: R1.1, U3.49
unnamed: C24.1, U8.14
unnamed: R50.1, U3.50
unnamed: R25.2, U8.30
unnamed: R32.2, U8.31
unnamed: JP1.2, U8.22
unnamed: R14.1, U3.46
unnamed: JP2.2, U8.24
unnamed: Q2.5, R23.2
unnamed: Q2.2, R29.2
unnamed: R39.2, U9.6
unnamed: R40.2, U9.5
unnamed: R41.1, U9.3
unnamed: R42.1, U9.4
unnamed: R35.1, U9.20
unnamed: R36.1, U9.21
unnamed: R37.1, U9.18
unnamed: R38.1, U9.19
unnamed: C32.1, FB2.2, R44.2
unnamed: JP4.1, R42.2
unnamed: D3.A, R51.1
unnamed: R52.2, U14.40
unnamed: R53.2, U14.39
unnamed: R89.1, U14.49
unnamed: R100.1, U14.50
unnamed: R93.1, U14.46
unnamed: Q1.5, R56.2
unnamed: Q1.2, R57.2
unnamed: R60.1, U17.8
unnamed: JP10.3, R62.2
unnamed: JP10.1, R63.2
unnamed: R90.1, U14.51
unnamed: C33.2, U13.2
unnamed: C50.1, C51.2, Q4.D1, Q4.G2, R66.1
unnamed: C55.2, R69.2, U21.33, Y2.3
unnamed: C56.2, R69.1, U21.32, Y2.1
unnamed: R68.1, U21.35
unnamed: R70.2, U21.28
unnamed: R71.2, U21.25
unnamed: C57.1, U21.34
unnamed: C58.1, U21.14
unnamed: R75.2, U21.30
unnamed: R76.2, U21.31
unnamed: JP11.2, U21.22
unnamed: JP12.2, U21.24
unnamed: R83.2, U23.6
unnamed: R84.2, U23.5
unnamed: R85.1, U23.3
unnamed: R86.1, U23.4
unnamed: R79.1, U23.20
unnamed: R80.1, U23.21
unnamed: R81.1, U23.18
unnamed: R82.1, U23.19
unnamed: C63.1, FB1.2, R87.2
unnamed: C64.2, U24.2
unnamed: JP13.1, R85.2
unnamed: JP14.1, R86.2
unnamed: D11.A, R101.1
unnamed: R102.2, U26.40
unnamed: R103.2, U26.39
unnamed: R139.1, U26.49
unnamed: R150.1, U26.50
unnamed: R143.1, U26.46
unnamed: Q5.5, R106.2
unnamed: Q5.2, R107.2
unnamed: R110.1, U29.8
unnamed: JP19.3, R112.2
unnamed: JP19.1, R113.2
unnamed: R140.1, U26.51
unnamed: C82.1, C83.2, Q6.D1, Q6.G2, R116.1
unnamed: C87.2, R119.2, U33.33, Y3.3
unnamed: C88.2, R119.1, U33.32, Y3.1
unnamed: R118.1, U33.35
unnamed: R120.2, U33.28
unnamed: R121.2, U33.25
unnamed: C89.1, U33.34
unnamed: C90.1, U33.14
unnamed: R125.2, U33.30
unnamed: R126.2, U33.31
unnamed: JP20.2, U33.22
unnamed: JP22.2, U33.24
unnamed: R133.2, U35.6
unnamed: R134.2, U35.5
unnamed: R135.1, U35.3
unnamed: R136.1, U35.4
unnamed: R129.1, U35.20
unnamed: R130.1, U35.21
unnamed: R131.1, U35.18
unnamed: R132.1, U35.19
unnamed: C95.1, FB3.2, R137.2
unnamed: C96.2, U36.2
unnamed: JP23.1, R135.2
unnamed: JP24.1, R136.2
unnamed: D16.A, R151.1
unnamed: R152.2, U38.40
unnamed: R153.2, U38.39
unnamed: R189.1, U38.49
unnamed: R200.1, U38.50
unnamed: R193.1, U38.46
unnamed: Q7.5, R156.2
unnamed: Q7.2, R157.2
unnamed: R160.1, U41.8
unnamed: JP29.3, R162.2
unnamed: JP29.1, R163.2
unnamed: R190.1, U38.51
unnamed: C114.1, C115.2, Q8.D1, Q8.G2, R166.1
unnamed: C119.2, R169.2, U45.33, Y4.3
unnamed: C120.2, R169.1, U45.32, Y4.1
unnamed: R168.1, U45.35
unnamed: R170.2, U45.28
unnamed: R171.2, U45.25
unnamed: C121.1, U45.34
unnamed: C122.1, U45.14
unnamed: R175.2, U45.30
unnamed: R176.2, U45.31
unnamed: JP30.2, U45.22
unnamed: JP31.2, U45.24
unnamed: R183.2, U47.6
unnamed: R184.2, U47.5
unnamed: R185.1, U47.3
unnamed: R186.1, U47.4
unnamed: R179.1, U47.20
unnamed: R180.1, U47.21
unnamed: R181.1, U47.18
unnamed: R182.1, U47.19
unnamed: C127.1, FB4.2, R187.2
unnamed: C128.2, U48.2
unnamed: JP32.1, R185.2
unnamed: JP33.1, R186.2
unnamed: D21.A, R201.1
unnamed: R202.2, U50.40
unnamed: R203.2, U50.39
unnamed: R239.1, U50.49
unnamed: R250.1, U50.50
unnamed: R243.1, U50.46
unnamed: Q9.5, R206.2
unnamed: Q9.2, R207.2
unnamed: R210.1, U53.8
unnamed: JP38.3, R212.2
unnamed: JP38.1, R213.2
unnamed: R240.1, U50.51
unnamed: C146.1, C147.2, Q10.D1, Q10.G2, R216.1
unnamed: C151.2, R219.2, U57.33, Y5.3
unnamed: C152.2, R219.1, U57.32, Y5.1
unnamed: R218.1, U57.35
unnamed: R220.2, U57.28
unnamed: R221.2, U57.25
unnamed: C153.1, U57.34
unnamed: C154.1, U57.14
unnamed: R225.2, U57.30
unnamed: R226.2, U57.31
unnamed: JP39.2, U57.22
unnamed: JP40.2, U57.24
unnamed: R233.2, U59.6
unnamed: R234.2, U59.5
unnamed: R235.1, U59.3
unnamed: R236.1, U59.4
unnamed: R229.1, U59.20
unnamed: R230.1, U59.21
unnamed: R231.1, U59.18
unnamed: R232.1, U59.19
unnamed: C159.1, FB5.2, R237.2
unnamed: C160.2, U60.2
unnamed: JP41.1, R235.2
unnamed: JP42.1, R236.2
unnamed: D26.A, R251.1
unnamed: R252.2, U62.40
unnamed: R253.2, U62.39
unnamed: R289.1, U62.49
unnamed: R300.1, U62.50
unnamed: R293.1, U62.46
unnamed: Q11.5, R256.2
unnamed: Q11.2, R257.2
unnamed: R260.1, U65.8
unnamed: JP47.3, R262.2
unnamed: JP47.1, R263.2
unnamed: R290.1, U62.51
unnamed: C178.1, C179.2, Q12.D1, Q12.G2, R266.1
unnamed: C183.2, R269.2, U69.33, Y6.3
unnamed: C184.2, R269.1, U69.32, Y6.1
unnamed: R268.1, U69.35
unnamed: R270.2, U69.28
unnamed: R271.2, U69.25
unnamed: C185.1, U69.34
unnamed: C186.1, U69.14
unnamed: R275.2, U69.30
unnamed: R276.2, U69.31
unnamed: JP48.2, U69.22
unnamed: JP49.2, U69.24
unnamed: R283.2, U71.6
unnamed: R284.2, U71.5
unnamed: R285.1, U71.3
unnamed: R286.1, U71.4
unnamed: R279.1, U71.20
unnamed: R280.1, U71.21
unnamed: R281.1, U71.18
unnamed: R282.1, U71.19
unnamed: C191.1, FB6.2, R287.2
unnamed: C192.2, U72.2
unnamed: JP50.1, R285.2
unnamed: JP51.1, R286.2
unnamed: D31.A, R301.1
unnamed: R302.2, U74.40
unnamed: R303.2, U74.39
unnamed: R339.1, U74.49
unnamed: R350.1, U74.50
unnamed: R343.1, U74.46
unnamed: Q13.5, R306.2
unnamed: Q13.2, R307.2
unnamed: R310.1, U77.8
unnamed: JP56.3, R312.2
unnamed: JP56.1, R313.2
unnamed: R340.1, U74.51
unnamed: C210.1, C211.2, Q14.D1, Q14.G2, R316.1
unnamed: C215.2, R319.2, U81.33, Y7.3
unnamed: C216.2, R319.1, U81.32, Y7.1
unnamed: R318.1, U81.35
unnamed: R320.2, U81.28
unnamed: R321.2, U81.25
unnamed: C217.1, U81.34
unnamed: C218.1, U81.14
unnamed: R325.2, U81.30
unnamed: R326.2, U81.31
unnamed: JP57.2, U81.22
unnamed: JP58.2, U81.24
unnamed: R333.2, U83.6
unnamed: R334.2, U83.5
unnamed: R335.1, U83.3
unnamed: R336.1, U83.4
unnamed: R329.1, U83.20
unnamed: R330.1, U83.21
unnamed: R331.1, U83.18
unnamed: R332.1, U83.19
unnamed: C223.1, FB7.2, R337.2
unnamed: C224.2, U84.2
unnamed: JP59.1, R335.2
unnamed: JP60.1, R336.2
unnamed: D36.A, R351.1
unnamed: R352.2, U86.40
unnamed: R353.2, U86.39
unnamed: R389.1, U86.49
unnamed: R400.1, U86.50
unnamed: R393.1, U86.46
unnamed: Q15.5, R356.2
unnamed: Q15.2, R357.2
unnamed: R360.1, U89.8
unnamed: JP66.3, R362.2
unnamed: JP66.1, R363.2
unnamed: R390.1, U86.51
unnamed: C242.1, C243.2, Q16.D1, Q16.G2, R366.1
unnamed: C247.2, R369.2, U93.33, Y8.3
unnamed: C248.2, R369.1, U93.32, Y8.1
unnamed: R368.1, U93.35
unnamed: R370.2, U93.28
unnamed: R371.2, U93.25
unnamed: C249.1, U93.34
unnamed: C250.1, U93.14
unnamed: R375.2, U93.30
unnamed: R376.2, U93.31
unnamed: JP67.2, U93.22
unnamed: JP68.2, U93.24
unnamed: R383.2, U95.6
unnamed: R384.2, U95.5
unnamed: R385.1, U95.3
unnamed: R386.1, U95.4
unnamed: R379.1, U95.20
unnamed: R380.1, U95.21
unnamed: R381.1, U95.18
unnamed: R382.1, U95.19
unnamed: C255.1, FB8.2, R387.2
unnamed: C256.2, U96.2
unnamed: JP69.1, R385.2
unnamed: JP70.1, R386.2
NEO_!RESET!: TP1.1, U9.8
NEO_!RESET!1: TP3.1, U23.8
NEO_!RESET!2: TP5.1, U35.8
NEO_!RESET!3: TP7.1, U47.8
NEO_!RESET!4: TP9.1, U59.8
NEO_!RESET!5: TP11.1, U71.8
NEO_!RESET!6: TP13.1, U83.8
NEO_!RESET!7: TP15.1, U95.8
NEO_!SAFEBOOT!: TP2.1, U9.1
NEO_!SAFEBOOT!1: TP4.1, U23.1
NEO_!SAFEBOOT!2: TP6.1, U35.1
NEO_!SAFEBOOT!3: TP8.1, U47.1
NEO_!SAFEBOOT!4: TP10.1, U59.1
NEO_!SAFEBOOT!5: TP12.1, U71.1
NEO_!SAFEBOOT!6: TP14.1, U83.1
NEO_!SAFEBOOT!7: TP16.1, U95.1
NEO_DM: R40.1, U8.6
NEO_DM1: R84.1, U21.6
NEO_DM2: R134.1, U33.6
NEO_DM3: R184.1, U45.6
NEO_DM4: R234.1, U57.6
NEO_DM5: R284.1, U69.6
NEO_DM6: R334.1, U81.6
NEO_DM7: R384.1, U93.6
NEO_DP: R39.1, U8.7
NEO_DP1: R83.1, U21.7
NEO_DP2: R133.1, U33.7
NEO_DP3: R183.1, U45.7
NEO_DP4: R233.1, U57.7
NEO_DP5: R283.1, U69.7
NEO_DP6: R333.1, U81.7
NEO_DP7: R383.1, U93.7
NEO_RF_IN: R43.2, U9.11, U13.6
NEO_RF_IN1: R88.2, U23.11, U24.6
NEO_RF_IN2: R138.2, U35.11, U36.6
NEO_RF_IN3: R188.2, U47.11, U48.6
NEO_RF_IN4: R238.2, U59.11, U60.6
NEO_RF_IN5: R288.2, U71.11, U72.6
NEO_RF_IN6: R338.2, U83.11, U84.6
NEO_RF_IN7: R388.2, U95.11, U96.6
POWER_BTN: C23.1, D4.C, J8.2, R31.1
POWER_BTN1: C51.1, D6.C, J17.2, R67.1
POWER_BTN2: C83.1, D12.C, J29.2, R117.1
POWER_BTN3: C115.1, D17.C, J40.2, R167.1
POWER_BTN4: C147.1, D22.C, J51.2, R217.1
POWER_BTN5: C179.1, D27.C, J62.2, R267.1
POWER_BTN6: C211.1, D32.C, J73.2, R317.1
POWER_BTN7: C243.1, D37.C, J84.2, R367.1
PPS: R49.1, U3.53
PPS1: R99.1, U14.53
PPS2: R149.1, U26.53
PPS3: R199.1, U38.53
PPS4: R249.1, U50.53
PPS5: R299.1, U62.53
PPS6: R349.1, U74.53
PPS7: R399.1, U86.53
PROG1: R6.2, U10.6
PROG2: R58.2, U17.6
PROG3: R108.2, U29.6
PROG4: R158.2, U41.6
PROG5: R208.2, U53.6
PROG6: R258.2, U65.6
PROG7: R308.2, U77.6
PROG8: R358.2, U89.6
RF_IN: C33.1, D5.1, FB2.1, J2.FEED
RF_IN1: C64.1, D10.1, FB1.1, J22.FEED
RF_IN2: C96.1, D15.1, FB3.1, J33.FEED
RF_IN3: C128.1, D20.1, FB4.1, J44.FEED
RF_IN4: C160.1, D25.1, FB5.1, J55.FEED
RF_IN5: C192.1, D30.1, FB6.1, J66.FEED
RF_IN6: C224.1, D35.1, FB7.1, J77.FEED
RF_IN7: C256.1, D40.1, FB8.1, J88.FEED
RTK_LV: R47.1, U3.20
RTK_LV1: R97.1, U14.20
RTK_LV2: R147.1, U26.20
RTK_LV3: R197.1, U38.20
RTK_LV4: R247.1, U50.20
RTK_LV5: R297.1, U62.20
RTK_LV6: R347.1, U74.20
RTK_LV7: R397.1, U86.20
RX2_LV: R46.1, U3.26
RX2_LV1: R96.1, U14.26
RX2_LV2: R146.1, U26.26
RX2_LV3: R196.1, U38.26
RX2_LV4: R246.1, U50.26
RX2_LV5: R296.1, U62.26
RX2_LV6: R346.1, U74.26
RX2_LV7: R396.1, U86.26
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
